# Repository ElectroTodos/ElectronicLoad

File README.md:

# ElectronicLoad
ElectronicLoad
youtube.com/electronicatodos/
https://www.youtube.com/playlist?list=PLbbu5mf7ZIfhO1j8X4gU5TwYUcYao87rT

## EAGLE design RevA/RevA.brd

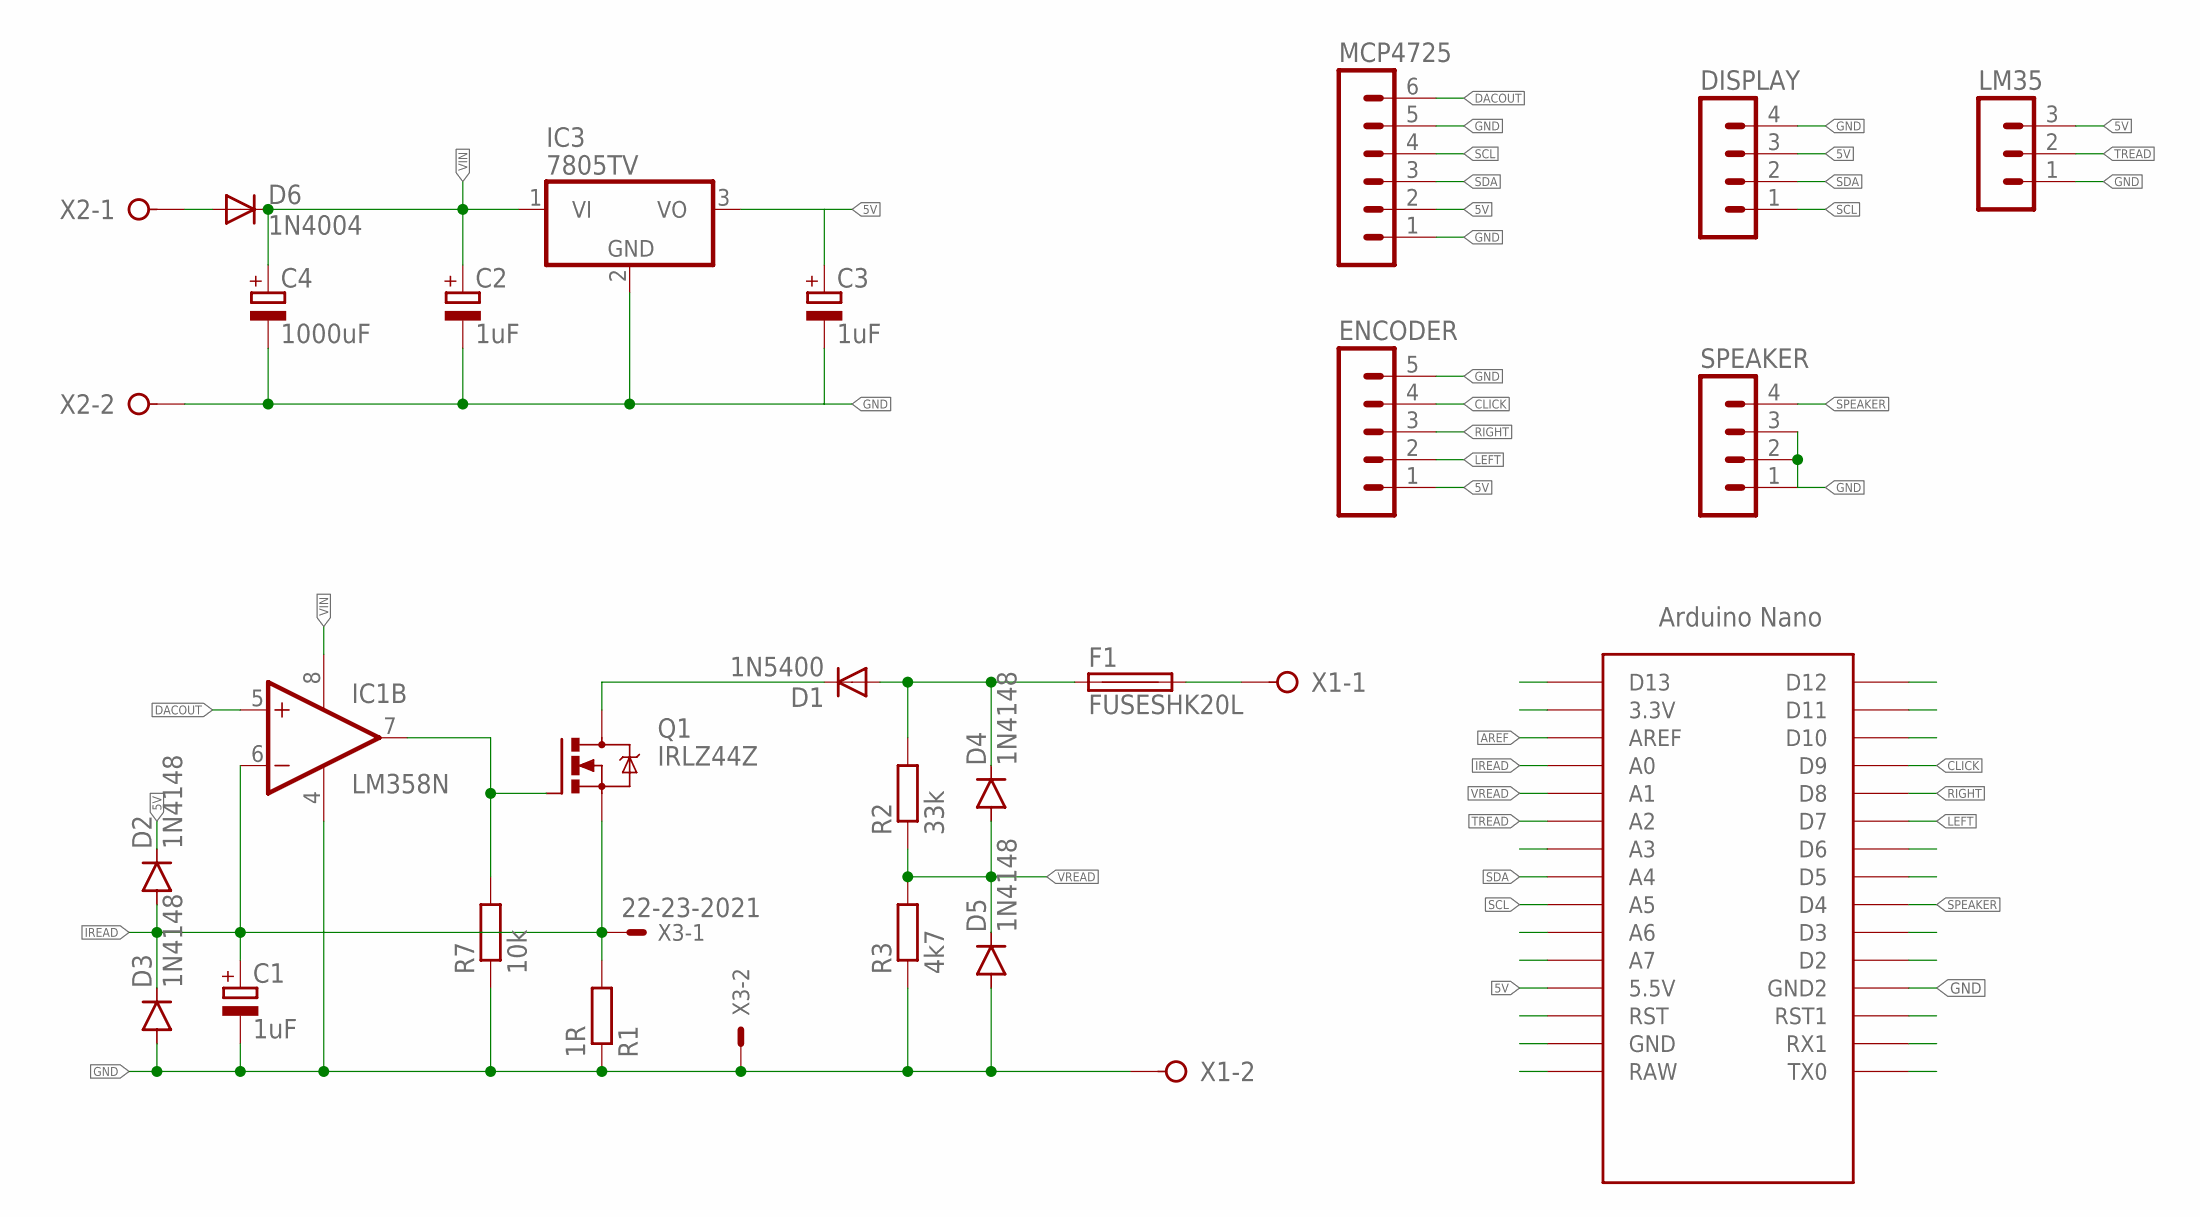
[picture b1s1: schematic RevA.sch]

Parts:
C1: 1uF; E2-5
C2, C3: 1uF; E5-5
C4: 1000uF; E5-10,5
D1: 1N5400; DO201-15
D2, D3, D4, D5: 1N4148; DIODE-1N4148
D6: 1N4004; DO41-10
DISPLAY: MA04-1
ENCODER: MA05-1
F1: FUSESHK20L; SHK20L
IC1: LM358N; DIL08
IC3: 7805TV; TO220V
LM35: MA03-1
MCP4725: MA06-1
Q1: IRLZ44Z; TO220BH
R1: 1R; 0309/12
R2: 33k; 0207/10
R3: 4k7; 0207/10
R7: 10k; 0207/10
SPEAKER: MA04-1
U$1: NANO
X1, X2: W237-02P; W237-132
X3: 22-23-2021

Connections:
5V: C3.+, D2.C, DISPLAY.3, ENCODER.1, IC3.3 (VO), LM35.3, MCP4725.2, U$1.5V (5.5V)
AREF: U$1.AREF
CLICK: ENCODER.4, U$1.D9
DACOUT: IC1.5 (+IN), MCP4725.6
GND: C1.-, C2.-, C3.-, C4.-, D3.A, D5.A, DISPLAY.4, ENCODER.5, IC1.4 (V-), IC3.2 (GND), LM35.1, MCP4725.1, MCP4725.5, R1.1, R3.1, R7.1, SPEAKER.1, SPEAKER.2, SPEAKER.3, U$1.GND1 (GND2), X1.2, X2.2, X3.2
IREAD: C1.+, D2.A, D3.C, IC1.6 (-IN), Q1.S, R1.2, U$1.A0, X3.1
LEFT: ENCODER.2, U$1.D7
unnamed: F1.2A (2), X1.1
unnamed: D1.A, D4.C, F1.1A (1), R2.2
unnamed: IC1.7 (OUT), Q1.G, R7.2
unnamed: D6.A, X2.1
unnamed: D1.C, Q1.D
RIGHT: ENCODER.3, U$1.D8
SCL: DISPLAY.1, MCP4725.4, U$1.A5
SDA: DISPLAY.2, MCP4725.3, U$1.A4
SPEAKER: SPEAKER.4, U$1.D4
TREAD: LM35.2, U$1.A2
VIN: C2.+, C4.+, D6.C, IC1.8 (V+), IC3.1 (VI)
VREAD: D4.A, D5.C, R2.1, R3.2, U$1.A1

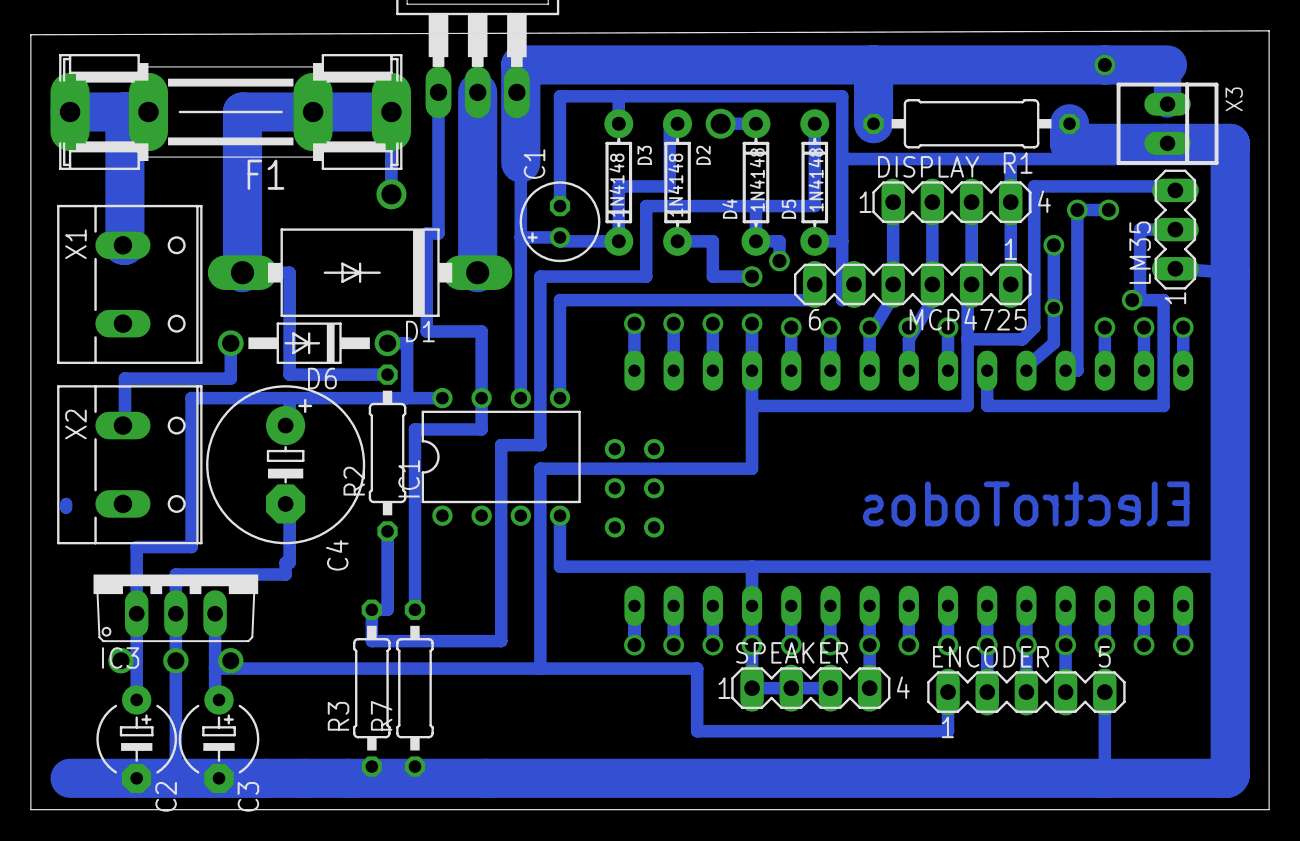
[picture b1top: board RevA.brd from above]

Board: 2 copper layers, 80.2 x 50.5 mm, 27 parts (0 on the bottom side), 18 nets.

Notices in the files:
parts and their libraries:
SparkFun-DiscreteSemi: Licensing: Creative Commons ShareAlike 4.0 International - https://creativecommons.org/licenses/by-sa/4.0
